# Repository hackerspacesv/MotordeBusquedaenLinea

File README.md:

Motor de Búsqueda en Línea
==========================
**Motor de Búsqueda en Línea** es el robot ganador del 2do Lugar en la competencia de seguidores de líneas en el ArduChallenge organizado por la <a href="https://www.facebook.com/ArduinoGuatemala/">Comunidad Arduino de Guatemala</a> el 27 de diciembre de 2017.

MBL es un proyecto de <a href="https://www.oshwa.org/definition/spanish/">Hardware Libre</a>. Todo el código fuente, archivos de diseño y documentación está disponible en este repositorio para cualquiera que desee utilizarlo o crear proyectos derivados del mismo.

Este proyecto ha sido desarrollado gracias a los aportes de Joksan Alvarado, Mario Gómez y Karla Hernández del <a href="http://hackerspace.teubi.co/">Hackerspace San Salvador</a>. El equipo del Hackerspace espera que este proyecto pueda ser replicado y utilizado para fines educativos en donde sea necesario.

¿Qué contiene este repositorio?
-------------------------------
El repositorio de MBL está organizado de la siguiente manera en las diferentes carpetas:

- **Datasheets**: Este directorio contiene las hojas técnicas de los chips utilizados en el diseño electrónico de MBL. 

- **Design**: Incluye todos los archivos de diseño mecánico y electrónico utilizados para la construcción del robot. Los archivos de diseño electrónico se pueden editar con <a href="https://www.autodesk.com/products/eagle/overview">EAGLE de Autodesk</a> y los archivos de diseño mecánico se pueden editar con <a href="https://www.freecadweb.org/">FreeCAD</a>. Esta carpeta también incluye las listas de materiales o BOM.

- **Documentation**: Esta carpeta contiene toda la documentación referente al código fuente provisto con MBL. La carpeta incluye desde notas de diseño, parámetros de configuración de protocolos de comunicación y la documentación de APIs para programadores.

- **Libraries**: Esta carpeta contienen bibliotecas de componentes utilizadas en los diseños de CAD.

- **Source**: Contiene los archivos de código fuente de la API para programadores y ejemplos básicos de uso de la misma para diferentes plataformas.

Los sub-directorios de cada carpeta podrían contener archivos *README.md* con información importante sobre el contenido de la misma.

¿Cómo utilizar MBL?
-------------------
Esta es una guía muy rápida (e incompleta) sobre cómo hacer construir y hacer funcionar a MBL.

**Hardware**:
>1. Adquiere todos los componentes especificados en el archivo *BOM.odx* en la carpeta *Design*.
>2. Corta el acrílico del chasis según los archivos de diseño provistos en la carpeta *Design/FreeCAD/SVG corte laser*.
>3. Fabrica las PCBs y ensambla según archivos de diseño en *Design/eagle*.
>4. Conecta todo según especificaciones y revisa que las conexiones eléctricas no estén cruzadas o contengan falso-contactos.

**Software**:
>1. Instala el soporte para Teensy con <a href="https://www.pjrc.com/teensy/td_download.html">Teensyduino</a>.
>2. Copia la carpeta *Source/Arduino/libraries/I32CTT* a tu carpeta de bibliotecas en Arduino.
>3. Utiliza el Sketch de ejemplo "Source/Arduino/I32CTT_PoC" para programar el robot.
>4. Utiliza el Sketch de ejemplo "Source/Arduino/I32CTT_PoC_Master" para programar controles remotos.

Si hasta este punto nada ha tomado fuego podrás utilizar MBL a través de control remoto. Modifica los ejemplos provistos para agregar funcionalidad adicional.

En la carpeta "Source/python" encontrarás también ejemplos de aplicación de control y comunitación al robot. Para ello necesitas una <a href="https://www.raspberrypi.org/">Raspberry Pi</a> y un <a href="http://openlabs.co/OSHW/Raspberry-Pi-802.15.4-radio">radio 802.15.4 de OpenLabs.co</a>.

Tecnologías utilizadas
----------------------
MBL no solo pretende ser un robot de uso específico sino una plataforma para la prueba y el desarrollo de soluciones del <a href="https://es.wikipedia.org/wiki/Internet_de_las_cosas">Internet de las Cosas (IoT)</a>. Por ello MBL hace uso de las siguientes tecnologías:

* **Procesamiento con ARM-Cortex**: <a href="https://www.arm.com/">ARM</a> es la arquitectura más utilizada en el desarrollo no solo de dispositivos móviles sino también de soluciones de IoT. MBL procesa toda la información utilizando la tarjeta electrónica <a href="https://www.pjrc.com/teensy/teensy31.html">PJRC Teensy 3.2</a> que utiliza un poderoso microcontrolador de <a href="https://www.nxp.com/products/processors-and-microcontrollers/arm-based-processors-and-mcus/kinetis-cortex-m-mcus/k-seriesperformancem4/k2x-usb/kinetis-k20-100-mhz-full-speed-usb-mixed-signal-integration-microcontrollers-based-on-arm-cortex-m4-core:K20_100">32-bits ARM Cortex-M4</a> corriendo a 96Mhz.
* **Comunicaciones inalámbricas con IEEE 802.15.4**: El estándar <a href="https://en.wikipedia.org/wiki/IEEE_802.15.4">IEEE 802.15.4</a> es la apuesta de <a href="https://www.ieee.org/index.html">IEEE</a> para las soluciones de IoT. Este protocolo de corto alcance y bajo ancho de banda resulta ideal para dispositivos con bajo poder de procesamiento y que requieren de un consumo mínimo de energía.
* **Control remoto y Telemetría con I32CTT**: Este protocolo desarrollado en casa por el Hackerspace San Salvador combina una especificación de mensajes cortos utilizando números enteros de 32 bits que puede ser transmitido sobre diferentes medios de comunicación. Actualmente se soportan puentes serie bluetooth e IEEE 802.15.4.

Licenciamiento
--------------
A menos que se especifique lo contrario en el archivo de código fuente, todo el código fuente incluído como parte de MBL se distribuye bajo la licencia <a href="https://www.gnu.org/licenses/gpl-3.0.en.html">GNU GPL v3.0</a>.

Todos los archivos de diseño mecánico, diseño electrónico y la documentación se distribuyen bajo la licencia Creative-Commons Attribution-ShareAlike 2.0 Generic (<a href="https://creativecommons.org/licenses/by-sa/2.0/">CC BY-SA 2.0</a>).

Archivos de documentación de terceros como hojas de datos u otros se incluyen en el repositorio sólo con fines informativos y los copyrights corresponden a sus respectivos dueños.

Todos los nombres de marcas y tecnologías mencionados en este README y documentación adjunta son propiedad de sus respectivos dueños y se utilizan solo con fines informativos.

Lo anterior implica que puedes copiar/modificar y redistribuir MBL para fines comerciales y no comerciales en tanto incluyas la información original de los autores y utilices licencias compatibles a las mencionadas anteriormente.

Información de contacto
-----------------------
Si deseas agregar funcionalidad adicional a MBL puedes enviar un *"pull request"* a este repositorio. De igual manera si encuentras algo que no funciona envíanos un *"issue"* para que podamos realizar las correcciones.

Si estás interesado en colaborar en algo más que código fuente y diseño como por ejemplo: Generar material educativo, implementar MBL en tu centro de estudios o realizar publicaciones o investigaciones tomando como base este proyecto, puedes contactarte con el equipo de desarrollo al correo electrónico <a href="mailto:info@teubi.co">info@teubi.co</a>.

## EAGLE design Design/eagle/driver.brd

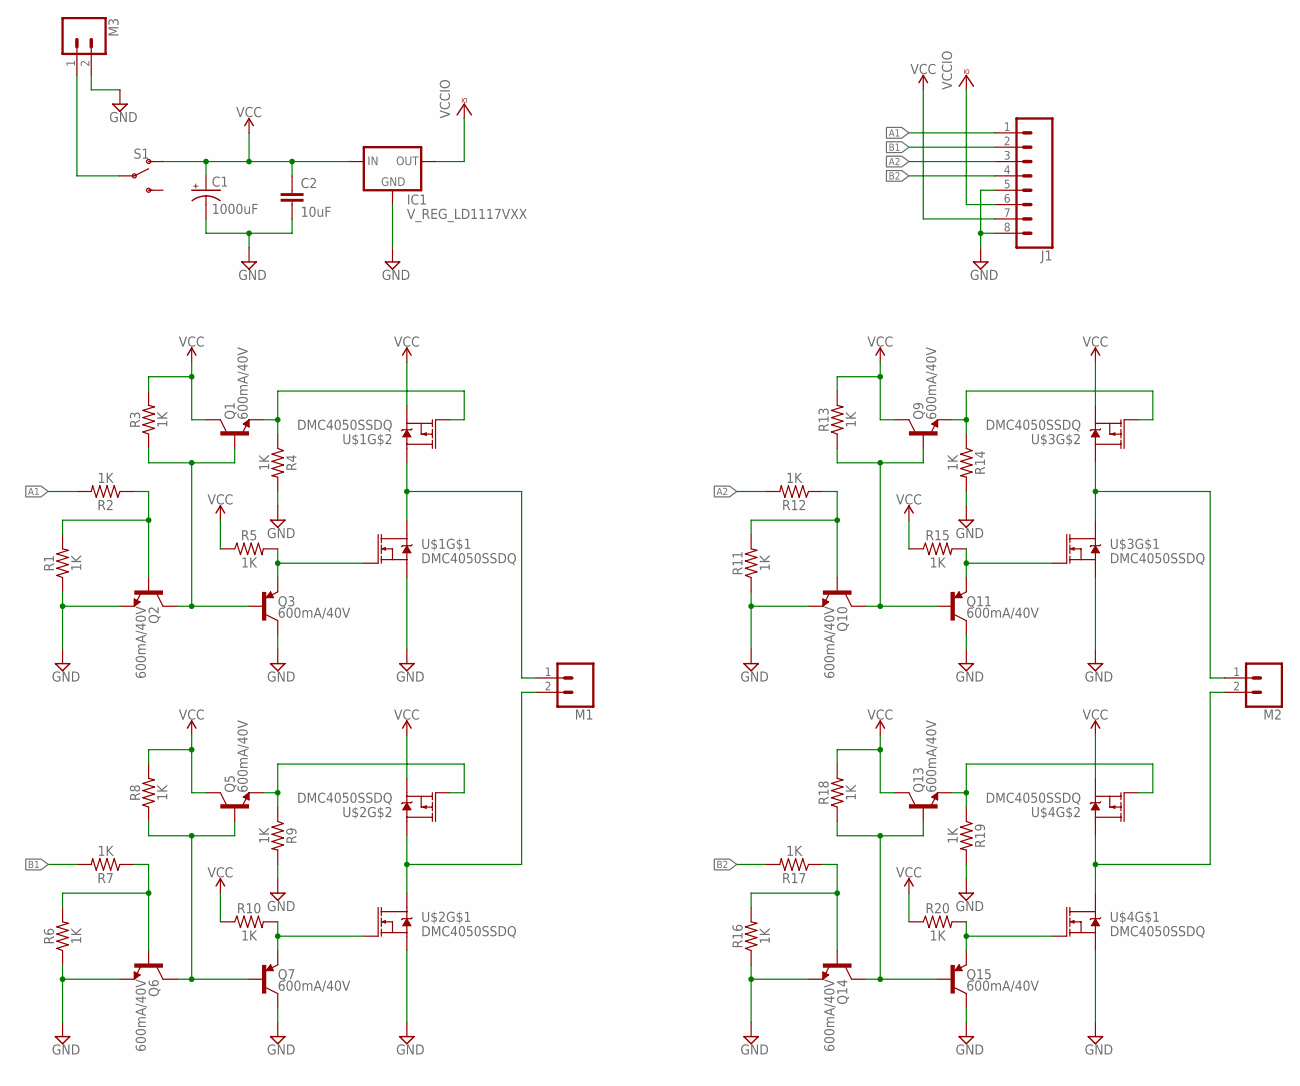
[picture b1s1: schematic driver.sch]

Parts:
C1: 1000uF; CPOL-RADIAL-5MM-10MM
C2: 10uF; 0805
IC1: V_REG_LD1117VXX; 78XXL
J1: CONN_08"; 1X08
M1, M2, M3: CONN_023.5MM; SCREWTERMINAL-3.5MM-2
Q1, Q2, Q3, Q5, Q6, Q7, Q9, Q10, Q11, Q13, Q14, Q15: 600mA/40V; SOT23-3
R1, R2, R3, R4, R5, R6, R7, R8, R9, R10, R11, R12, R13, R14, R15, R16, R17, R18, R19, R20: 1K; 0805
S1: SWITCH-SPDT-PTH-11.6X4.0MM; SWITCH_SPDT_PTH_11.6X4.0MM
U$1, U$2, U$3, U$4: DMC4050SSDQ; SO08

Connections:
A1: J1.1, R2.2
A2: J1.3, R12.2
B1: J1.2, R7.2
B2: J1.4, R17.2
GND: C1.-, C2.2, IC1.IN (GND), J1.5, J1.8, M3.2, Q2.2 (E), Q3.3 (C), Q6.2 (E), Q7.3 (C), Q10.2 (E), Q11.3 (C), Q14.2 (E), Q15.3 (C), R1.1, R4.2, R6.1, R9.2, R11.1, R14.2, R16.1, R19.2, U$1.1 (S), U$2.1 (S), U$3.1 (S), U$4.1 (S)
M1B: M1.2, U$2.5 (D), U$2.6 (D), U$2.7 (D), U$2.8 (D)
M1T: M1.1, U$1.5 (D), U$1.6 (D), U$1.7 (D), U$1.8 (D)
M2B: M2.2, U$4.5 (D), U$4.6 (D), U$4.7 (D), U$4.8 (D)
M2T: M2.1, U$3.5 (D), U$3.6 (D), U$3.7 (D), U$3.8 (D)
unnamed: Q2.1 (B), R1.2, R2.1
unnamed: Q1.1 (B), Q2.3 (C), Q3.1 (B), R3.1
unnamed: Q3.2 (E), R5.2, U$1.2 (G)
unnamed: Q6.1 (B), R6.2, R7.1
unnamed: Q5.1 (B), Q6.3 (C), Q7.1 (B), R8.1
unnamed: Q7.2 (E), R10.2, U$2.2 (G)
unnamed: Q1.2 (E), R4.1, U$1.4 (G)
unnamed: Q10.1 (B), R11.2, R12.1
unnamed: Q9.1 (B), Q10.3 (C), Q11.1 (B), R13.1
unnamed: Q5.2 (E), R9.1, U$2.4 (G)
unnamed: Q11.2 (E), R15.2, U$3.2 (G)
unnamed: Q9.2 (E), R14.1, U$3.4 (G)
unnamed: Q14.1 (B), R16.2, R17.1
unnamed: Q13.1 (B), Q14.3 (C), Q15.1 (B), R18.1
unnamed: Q15.2 (E), R20.2, U$4.2 (G)
unnamed: Q13.2 (E), R19.1, U$4.4 (G)
unnamed: M3.1, S1.2
VCC: C1.+, C2.1, IC1.OUT (IN), J1.7, Q1.3 (C), Q5.3 (C), Q9.3 (C), Q13.3 (C), R3.2, R5.1, R8.2, R10.1, R13.2, R15.1, R18.2, R20.1, S1.1 (O), U$1.3 (S), U$2.3 (S), U$3.3 (S), U$4.3 (S)
VCCIO: IC1.GND (OUT), J1.6

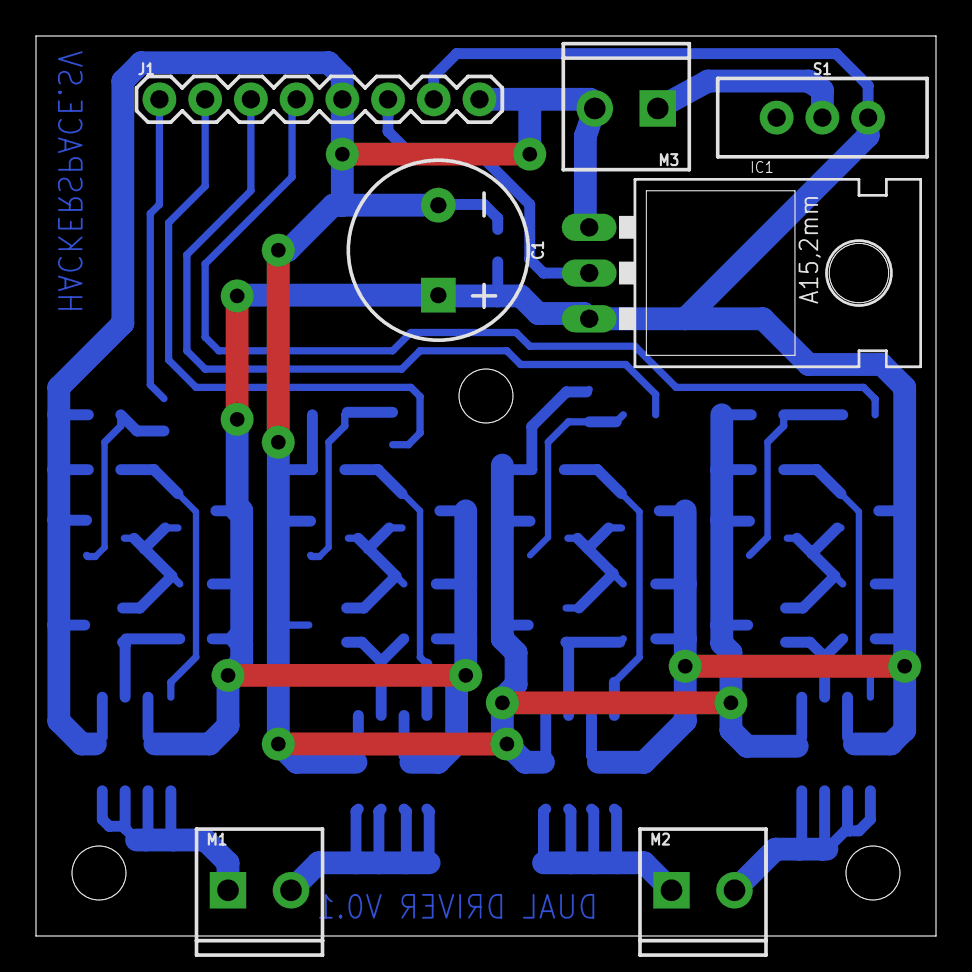
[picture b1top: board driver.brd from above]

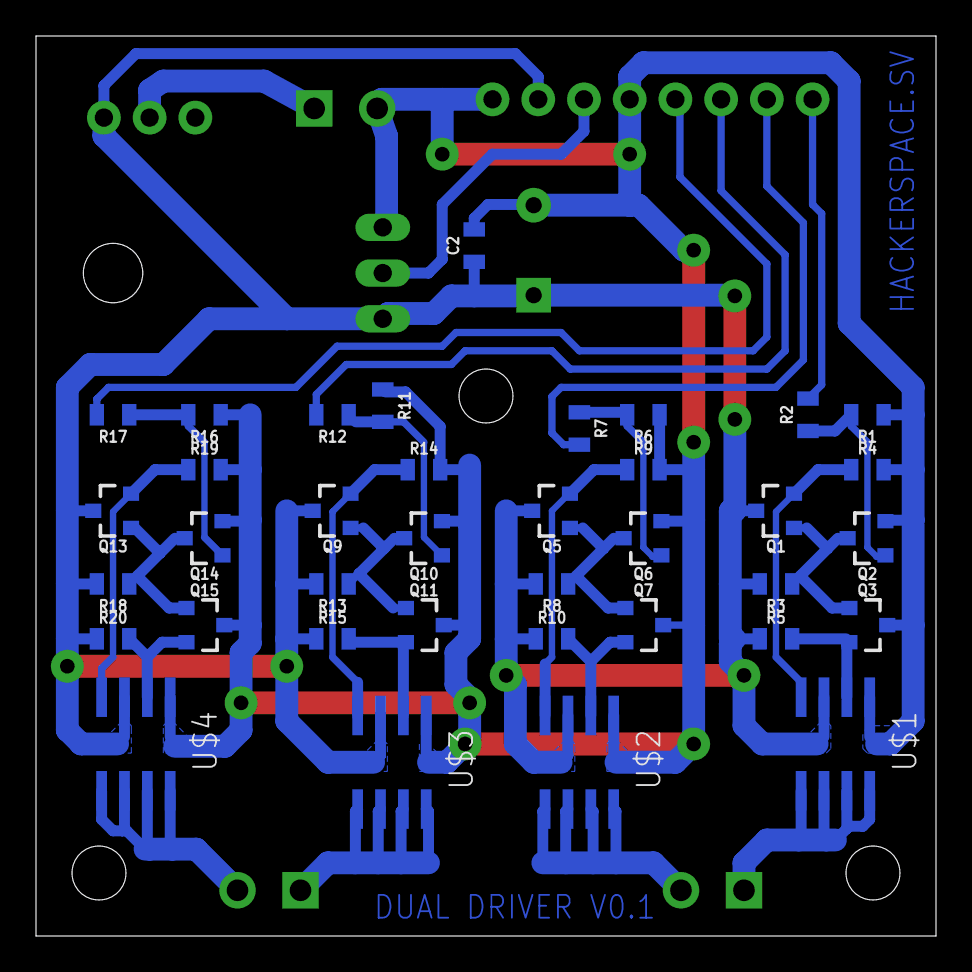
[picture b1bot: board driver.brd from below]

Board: 2 copper layers, 50.0 x 50.0 mm, 44 parts (37 on the bottom side), 28 nets.

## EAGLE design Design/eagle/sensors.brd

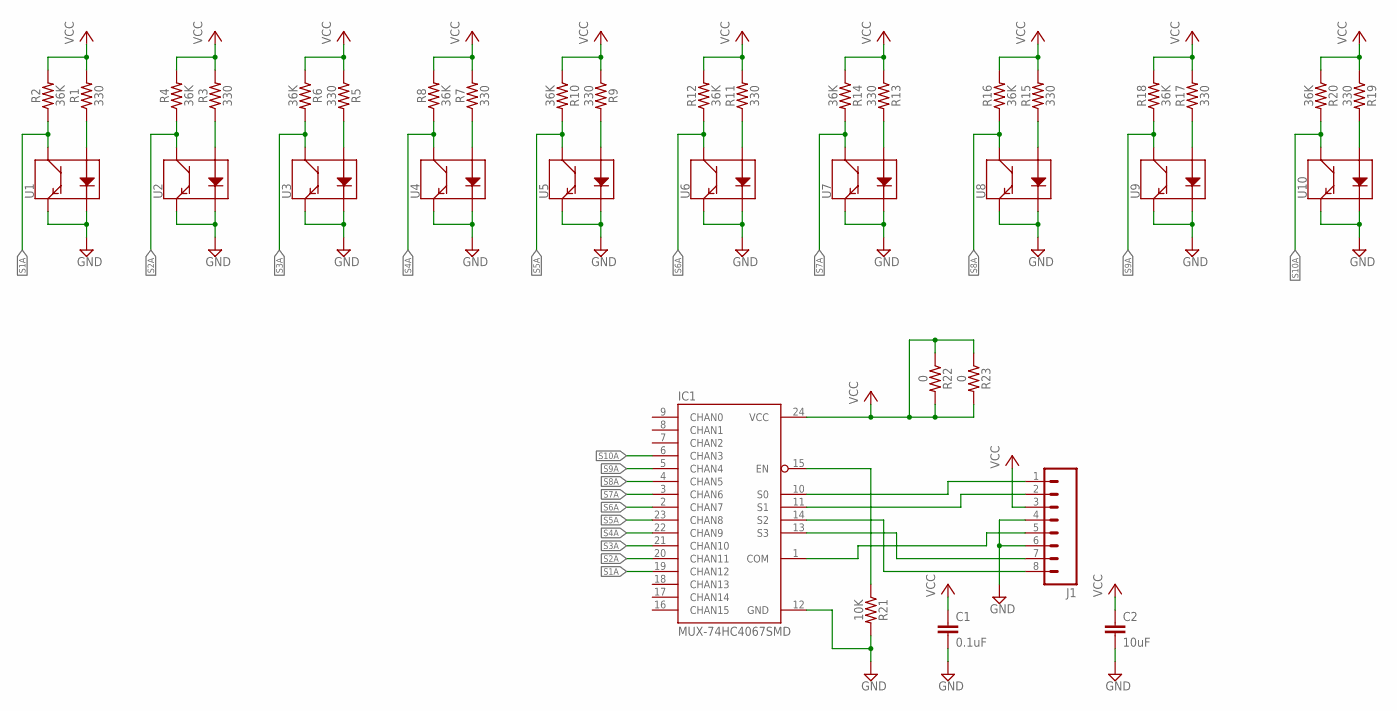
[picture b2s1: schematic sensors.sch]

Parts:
C1: 0.1uF; 0805
C2: 10uF; 0805
IC1: MUX-74HC4067SMD; SSOP24
J1: M08; 1X08_ROUND
R1, R3, R5, R7, R9, R11, R13, R15, R17, R19: 330; 0805
R2, R4, R6, R8, R10, R12, R14, R16, R18, R20: 36K; 0805
R21: 10K; 0805
R22, R23: 0; 0805
U1, U2, U3, U4, U5, U6, U7, U8, U9, U10: QRE1113SMD-W; QRE1113-W

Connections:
GND: C1.2, C2.2, IC1.12 (GND), J1.4, J1.6, R21.2, U1.2 (K), U1.4 (E), U2.2 (K), U2.4 (E), U3.2 (K), U3.4 (E), U4.2 (K), U4.4 (E), U5.2 (K), U5.4 (E), U6.2 (K), U6.4 (E), U7.2 (K), U7.4 (E), U8.2 (K), U8.4 (E), U9.2 (K), U9.4 (E), U10.2 (K), U10.4 (E)
unnamed: R1.1, U1.1 (A)
unnamed: IC1.13 (S3), J1.7
unnamed: R3.1, U2.1 (A)
unnamed: IC1.15 (EN), R21.1
unnamed: R5.2, U3.1 (A)
unnamed: IC1.14 (S2), J1.8
unnamed: R7.1, U4.1 (A)
unnamed: IC1.10 (S0), J1.1
unnamed: R9.2, U5.1 (A)
unnamed: IC1.11 (S1), J1.2
unnamed: R11.1, U6.1 (A)
unnamed: IC1.1 (COM), J1.5
unnamed: R13.2, U7.1 (A)
unnamed: R15.1, U8.1 (A)
unnamed: R17.1, U9.1 (A)
unnamed: R19.2, U10.1 (A)
S1A: IC1.19 (CHAN12), R2.1, U1.3 (C)
S2A: IC1.20 (CHAN11), R4.1, U2.3 (C)
S3A: IC1.21 (CHAN10), R6.2, U3.3 (C)
S4A: IC1.22 (CHAN9), R8.1, U4.3 (C)
S5A: IC1.23 (CHAN8), R10.2, U5.3 (C)
S6A: IC1.2 (CHAN7), R12.1, U6.3 (C)
S7A: IC1.3 (CHAN6), R14.2, U7.3 (C)
S8A: IC1.4 (CHAN5), R16.1, U8.3 (C)
S9A: IC1.5 (CHAN4), R18.1, U9.3 (C)
S10A: IC1.6 (CHAN3), R20.2, U10.3 (C)
VCC: C1.1, C2.1, IC1.24 (VCC), J1.3, R1.2, R2.2, R3.2, R4.2, R5.1, R6.1, R7.2, R8.2, R9.1, R10.1, R11.2, R12.2, R13.1, R14.1, R15.2, R16.2, R17.2, R18.2, R19.1, R20.1, R22.1, R22.2, R23.1, R23.2

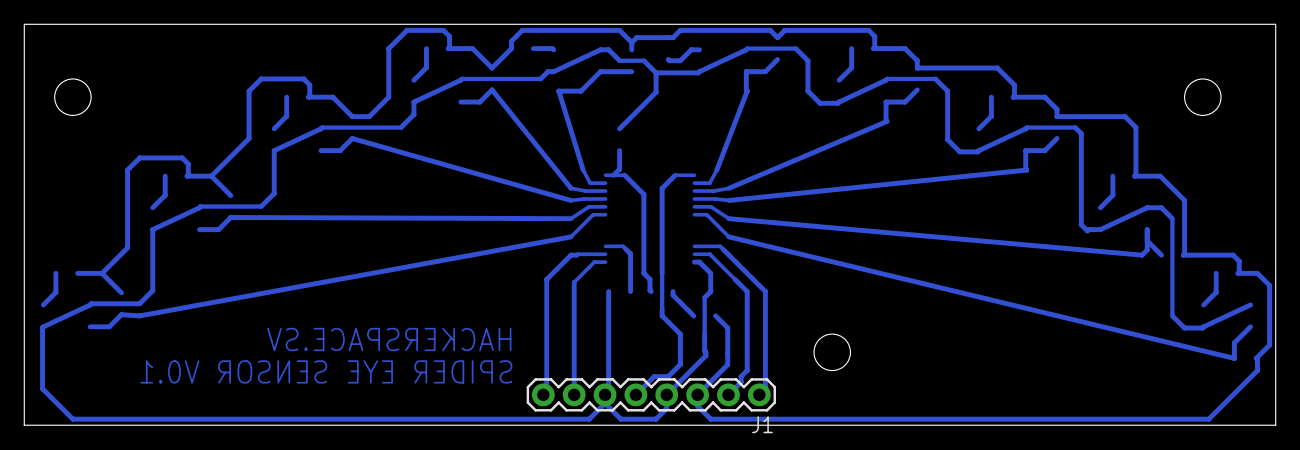
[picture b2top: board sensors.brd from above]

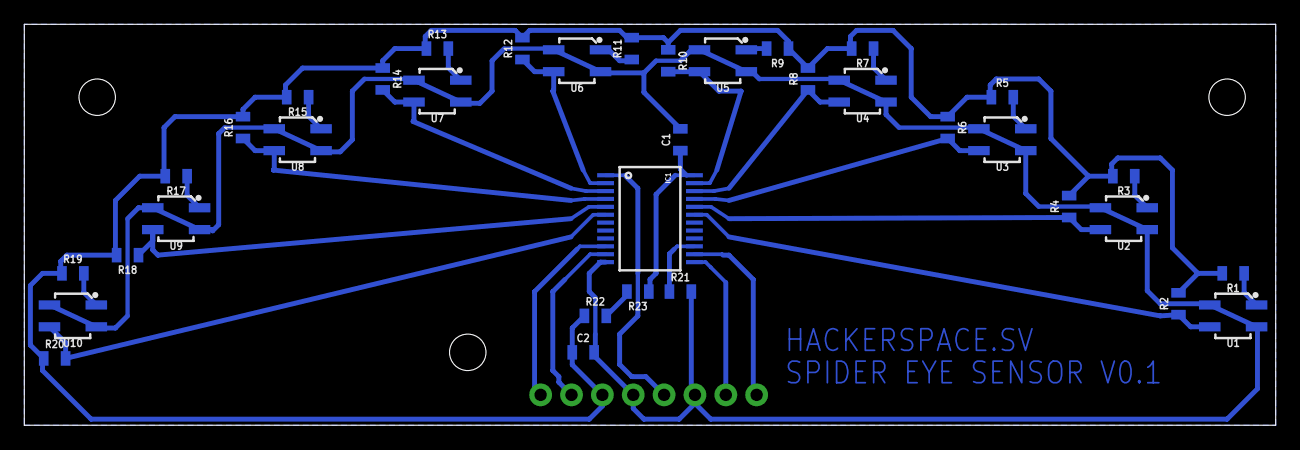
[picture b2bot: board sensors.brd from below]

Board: 2 copper layers, 103.0 x 33.0 mm, 37 parts (36 on the bottom side), 28 nets.

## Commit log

2017-11-02 Cambiando licencia gpl2 por gpl3 luego de platicas interesantes.
2017-11-02 Agregando el archivo de lectura de la gpl3, leelo esta interesante.
2017-11-13 Agregado circuito y PCB driver de motor.
2017-11-13 Correcciones al PCB
2017-11-13 Removidos vias sobrepuestos automaticamente.
2017-11-13 Agregada distribucion PCB sensores
2017-11-15 Finished sensor PCB + Analog MUX
2017-11-15 Fixed missing COM line from analog MUX
2017-11-18 Agregados ajustes en PCB para fotosensibilizada.
2017-11-19 Agregadas correcciones en PCB
2017-11-20 [CAD] Agregados todos los archivos de FreeCAD y archivos de corte laser en SVG.
2017-11-20 [Documentacion] Agregadas hojas de datos de BJT NPN, Mux analogo y sensor reflectivo.
2017-11-21 Actualizando README
2017-11-25 Archivos de FreeCAD movidos a carpeta Design
2017-11-25 Agregado Sketch para prueba de sensor.
2017-11-25 Corregida nota de Copyright en PruebaSensordeLinea.
2017-11-28 Agregado Null driver telemetria.
2017-11-28 Agregada interfaz de red nula.
2017-11-29 Agregado parser de protocolo. --No probado--
2017-11-30 Cambio en nombre protocolo HS2VT2 -> I32CTT
2017-11-30 Agregado transporte Stream para Arduino
2017-12-02 Finalizado PoC con implementacion parcial.
2017-12-02 Modificada estructura del paquete.
2017-12-02 Arreglado bug de alojamiento de memoria.
2017-12-03 Agregado modo manual. --No probado--
2017-12-05 I32CTT estructurada como Biblioteca
2017-12-10 Agregados cambios en la API.
2017-12-11 Varios cambios en API. Stub para AT86RF233.
2017-12-11 Engrosado el acrilico a 3mm y agregado espacio vertical para los motores dentro del chassis.
2017-12-16 Agregada maquina de estados radio 802.15.4
2017-12-17 Agregado soporte para IEEE 802.15.4 en Arduino.
2017-12-17 Agregados los archivos de codigo fuente con soporte para Raspberry Pi.
2017-12-18 Agregada respuesta automatica a origen. Corregido error en generacion de paquete en master. Cambios minimos en API de Interfaz de red
2017-12-18 Agregada documentacion FCF para IEEE 802.15.4
2017-12-18 Removida hoja de datos duplicada.
2017-12-22 Agregado soporte de introspeccion de I32CTT
2017-12-23 Probados radios en MBL. Separado ejemplo Master/Esclavo.
2017-12-23 Completado el programa de control para raspberry pi.
    - Agregado soporte de descodificacion de tramas 802.15.4
    - Implementado el protocolo i32ctt
    - Implementada la aplicacion de kivy para raspberry pi (control remoto)
2017-12-23 Agregado README para RC-1.
2017-12-23 Correccion al README
2017-12-26 Ampliado el codigo de gui para MBL en el port de raspberry pi.
    - [gui] Reestructurado el codigo, mejorando modularidad.
    - [gui] Implementado endpoint de control automatico.
    - [i32ctt] Ajustado el timeout de los paquetes.
    - [MAC], [PHY] Implementados los drivers nulos para MAC y PHY.
    - [PHY], [BUGFIX] Corregida la forma en que se calcula el timeout para comunicacion SPI.
2017-12-28 Corregido codigo prueba sensores. Corregido bug reportado por Joksan en endpoint I32CTT.
2017-12-28 Completada la interfaz grafica del endpoint automatico.
2017-12-28 Cambios para mostar en el hangout luego del arduchallege
2017-12-31 Aumentada velocidad de SPI a 1Mbps
2017-12-31 Correcciones al README.
2018-06-14 I32CTT cambiado a submodulo dentro de MBL.
2018-06-14 Actualizado el submodulo I32CTT
2018-06-16 Actualizado el submodulo I32CTT.

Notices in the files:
parts and their libraries:
SparkFun-Connectors: Licensing: Creative Commons ShareAlike 4.0 International - https://creativecommons.org/licenses/by-sa/4.0
